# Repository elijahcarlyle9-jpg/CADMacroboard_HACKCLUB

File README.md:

# CADMacroboard_HACKCLUB
        This is my subsission for Hackpad! 

# Fetures
        4 keys
        Customizable code
        Pre-Wrtitten code for Fusion 360 CAD shortcuts
        2 WS2812B RGB LEDs. One for underglow, and one that diffuses throughout the case

# CAD Model:

# PCB and Schematic

# Specifications
 # BOM:

        4x Cherry MX Switches
        2x SK6812 MINI Leds
        1x XIAO RP2040
        4x Blank DSA Keycaps
        4x M3x16 Bolt
        4x M3 Heatset
 # Others:

        KMK Firmware
        Top Case.stl
        Bottom Case.stl

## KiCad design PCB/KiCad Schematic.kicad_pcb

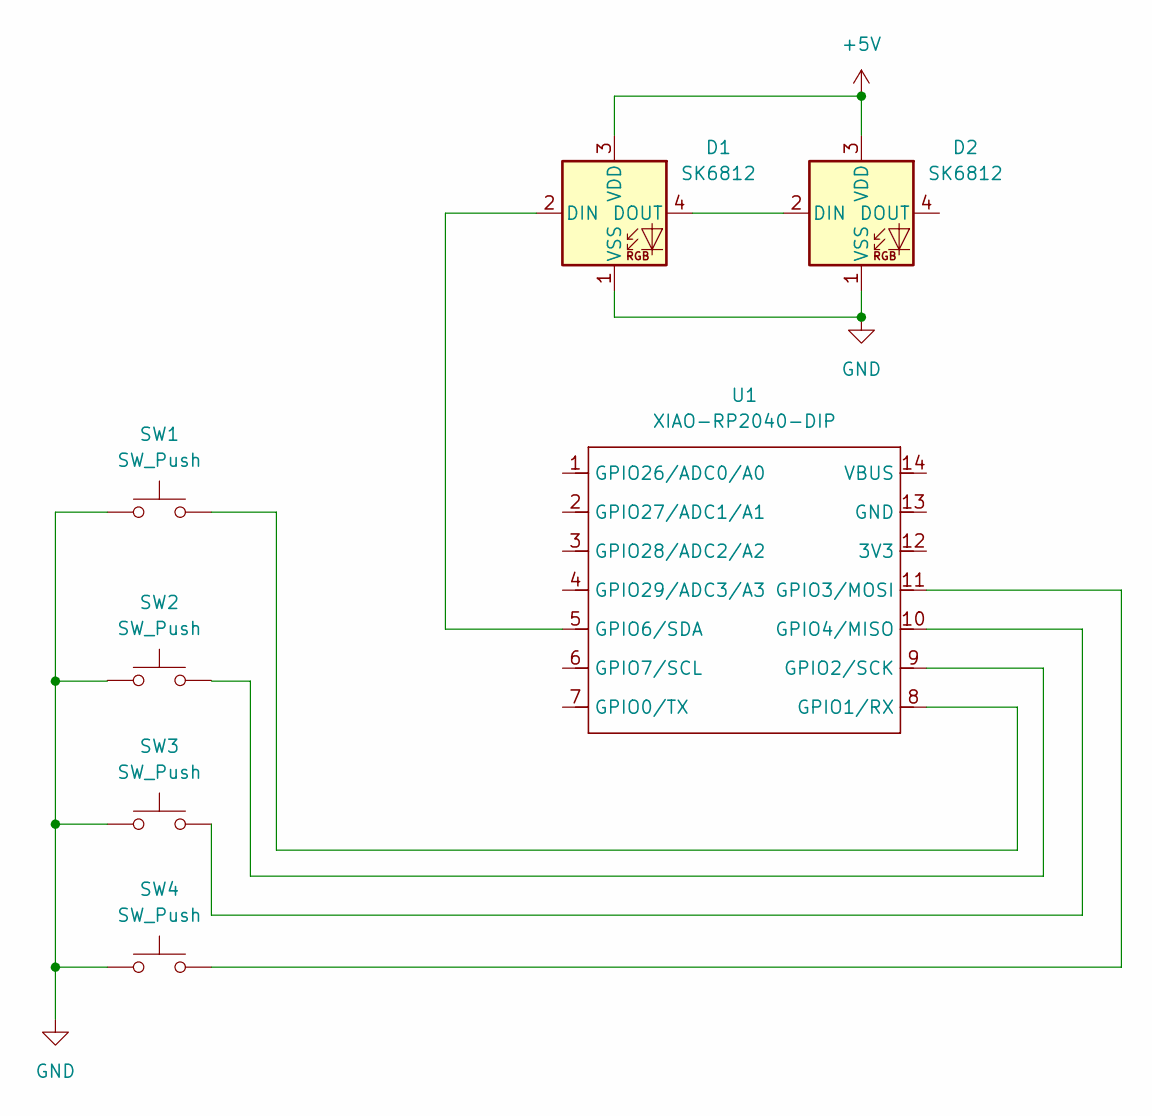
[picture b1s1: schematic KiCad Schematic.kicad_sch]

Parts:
D1, D2: SK6812; LED_SK6812MINI_PLCC4_3.5x3.5mm_P1.75mm
SW1, SW2, SW3, SW4: SW_Push; SW_Cherry_MX_1.00u_PCB
U1: XIAO-RP2040-DIP

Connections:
+5V: D1.3 (VDD), D2.3 (VDD)
GND: D1.1 (VSS), D2.1 (VSS), SW1.1, SW3.1, SW4.1
unnamed: D1.2 (DIN), U1.5 (GPIO6/SDA)
unnamed: D1.4 (DOUT), D2.2 (DIN)
unnamed: SW1.2, U1.8 (GPIO1/RX)
unnamed: SW4.2, U1.11 (GPIO3/MOSI)
unnamed: SW3.2, U1.10 (GPIO4/MISO)

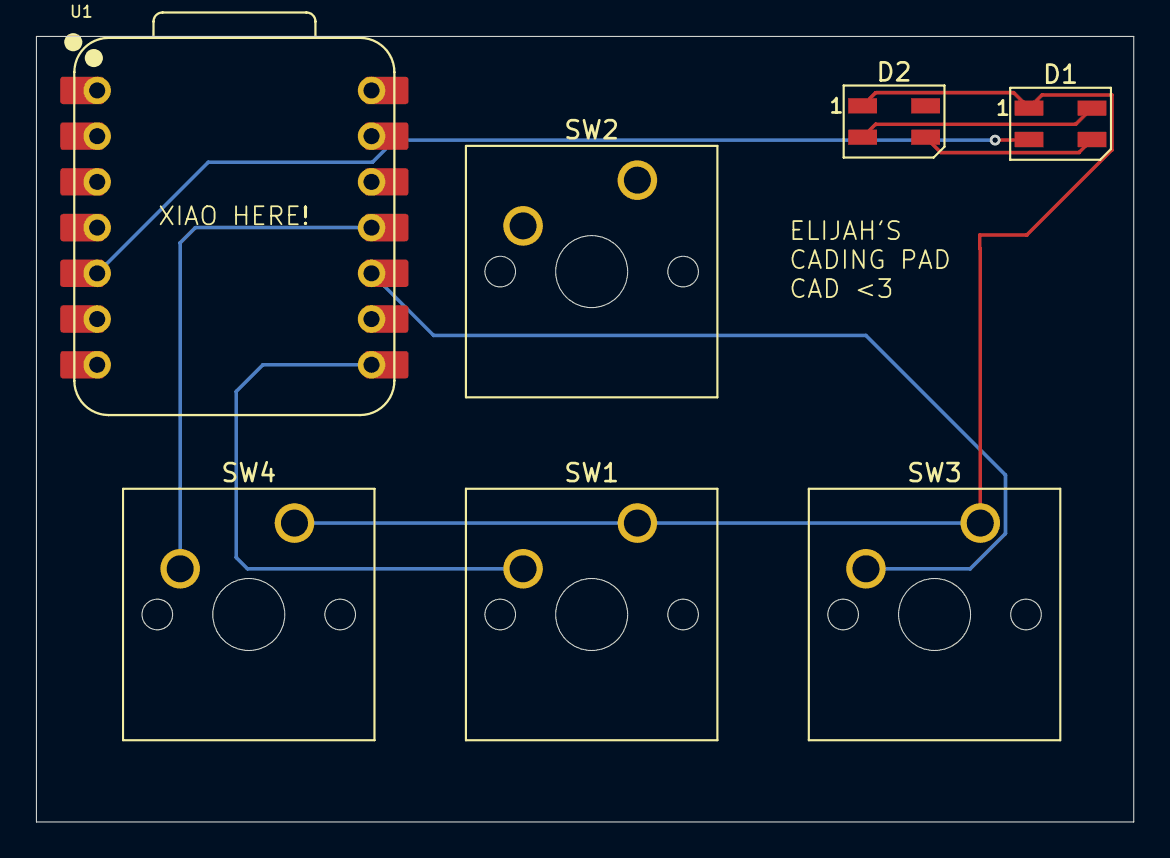
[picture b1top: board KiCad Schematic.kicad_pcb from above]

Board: 2 copper layers, 61.0 x 43.6 mm, 7 parts (0 on the bottom side), 7 nets.

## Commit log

2026-01-19 Create CAD (Casing, RP2040, and PCB)
2026-01-19 Delete CAD (Casing, RP2040, and PCB)
    Wrong File
2026-01-19 Create CAD
    Full CAD microcontroller, PCB, and Case
    Download go into a CAD software delete microcontroller, and PCB and separate top and bottom of case.
2026-01-19 Create PCB
    Download open up you should have:
    .kicadpro
    .kicadsch
    .kicad_pcb files
2026-01-19 Create Firmware
    Python using KMK download and upload into your device
    <Feel free to customize to your liking>
2026-01-19 Delete PCB
    Wrong File Format
2026-01-19 Delete CAD
    Wrong file format
2026-01-19 Delete Firmware
    Wrong file format
2026-01-19 Create CAD
2026-01-19 Add CAD Macroboard Bottom.step file
